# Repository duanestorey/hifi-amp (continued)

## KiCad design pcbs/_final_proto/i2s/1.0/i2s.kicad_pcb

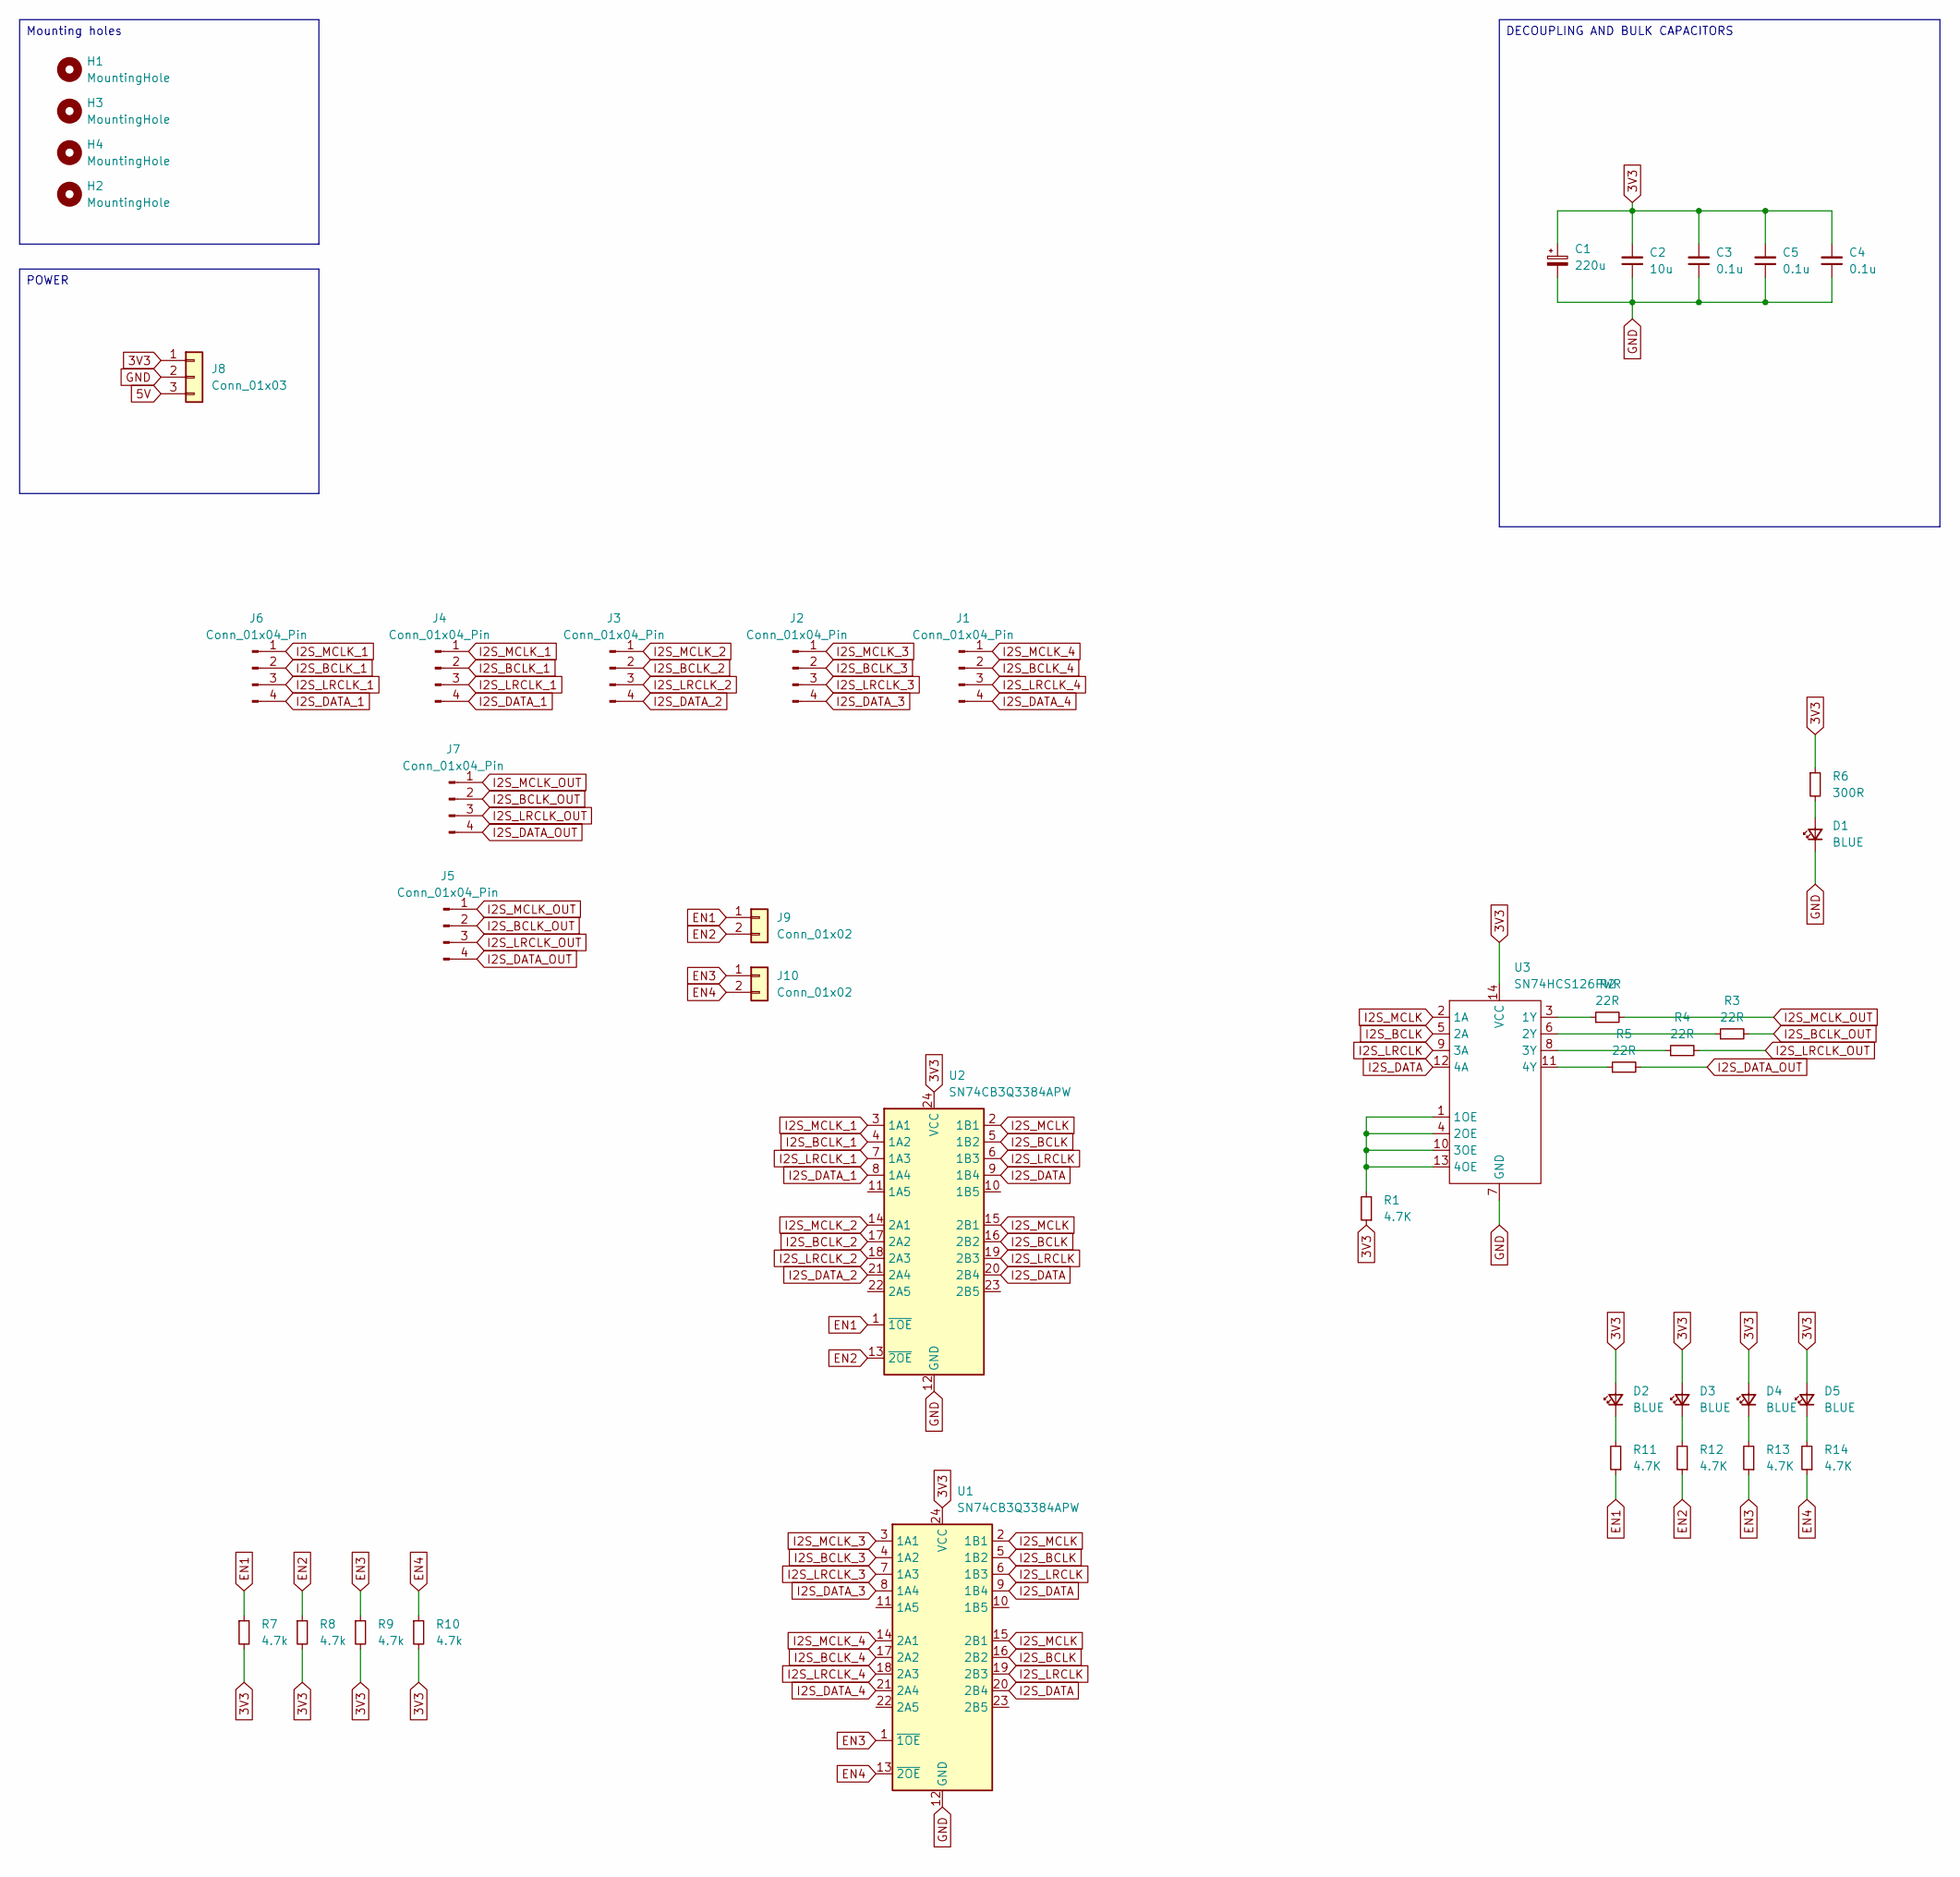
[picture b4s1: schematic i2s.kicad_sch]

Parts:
C1: 220u; CP_Elec_6.3x7.7
C2: 10u; C_1206_3216Metric_Pad1.33x1.80mm_HandSolder_Duane
C3, C4, C5: 0.1u; C_0805_2012Metric_Pad1.18x1.45mm_HandSolder_Duane
D1, D2, D3, D4, D5: BLUE; LED_0805_2012Metric_Pad_HandSolder_Duane
H1, H2, H3, H4: MountingHole; MountingHole_3.2mm_M3_DIN965_Pad_TopBottom
J1, J2, J3, J4, J6, J7: Conn_01x04_Pin; JST_PH_B4B-PH-K_1x04_P2.00mm_Vertical
J5: Conn_01x04_Pin; PinHeader_1x04_P2.54mm_Vertical
J8: Conn_01x03; JST_PH_B3B-PH-K_1x03_P2.00mm_Vertical
J9, J10: Conn_01x02; JST_PH_B2B-PH-K_1x02_P2.00mm_Vertical
R1, R11, R12, R13, R14: 4.7K; R_0805_2012Metric_Pad1.20x1.40mm_HandSolder_Duane
R2, R3, R4, R5: 22R; R_0805_2012Metric_Pad1.20x1.40mm_HandSolder_Duane
R6: 300R; R_0805_2012Metric_Pad1.20x1.40mm_HandSolder_Duane
R7, R8, R9, R10: 4.7k; R_0805_2012Metric_Pad1.20x1.40mm_HandSolder_Duane
U1, U2: SN74CB3Q3384APW; TSSOP-24_4.4x7.8mm_P0.65mm; Mouser SN74CB3Q3384APWR
U3: SN74HCS126PWR; TSSOP-14_4.4x5mm_P0.65mm; Mouser SN74HCS126PWR

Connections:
3V3: C1.1, C2.2, C3.2, C4.2, C5.2, D2.2 (A), D3.2 (A), D4.2 (A), D5.2 (A), J8.1, R1.1, R6.1, R7.2, R8.2, R9.2, R10.2, U1.24 (VCC), U2.24 (VCC), U3.14 (VCC)
5V: J8.3
EN1: J9.1, R7.1, R11.1, U2.1 (~1OE)
EN2: J9.2, R8.1, R12.1, U2.13 (~2OE)
EN3: J10.1, R9.1, R13.1, U1.1 (~1OE)
EN4: J10.2, R10.1, R14.1, U1.13 (~2OE)
GND: C1.2, C2.1, C3.1, C4.1, C5.1, D1.1 (K), J8.2, U1.12 (GND), U2.12 (GND), U3.7 (GND)
I2S_BCLK: U1.5 (1B2), U1.16 (2B2), U2.5 (1B2), U2.16 (2B2), U3.5 (2A)
I2S_BCLK_1: J4.2, J6.2, U2.4 (1A2)
I2S_BCLK_2: J3.2, U2.17 (2A2)
I2S_BCLK_3: J2.2, U1.4 (1A2)
I2S_BCLK_4: J1.2, U1.17 (2A2)
I2S_BCLK_OUT: J5.2, J7.2, R3.2
I2S_DATA: U1.9 (1B4), U1.20 (2B4), U2.9 (1B4), U2.20 (2B4), U3.12 (4A)
I2S_DATA_1: J4.4, J6.4, U2.8 (1A4)
I2S_DATA_2: J3.4, U2.21 (2A4)
I2S_DATA_3: J2.4, U1.8 (1A4)
I2S_DATA_4: J1.4, U1.21 (2A4)
I2S_DATA_OUT: J5.4, J7.4, R5.2
I2S_LRCLK: U1.6 (1B3), U1.19 (2B3), U2.6 (1B3), U2.19 (2B3), U3.9 (3A)
I2S_LRCLK_1: J4.3, J6.3, U2.7 (1A3)
I2S_LRCLK_2: J3.3, U2.18 (2A3)
I2S_LRCLK_3: J2.3, U1.7 (1A3)
I2S_LRCLK_4: J1.3, U1.18 (2A3)
I2S_LRCLK_OUT: J5.3, J7.3, R4.2
I2S_MCLK: U1.2 (1B1), U1.15 (2B1), U2.2 (1B1), U2.15 (2B1), U3.2 (1A)
I2S_MCLK_1: J4.1, J6.1, U2.3 (1A1)
I2S_MCLK_2: J3.1, U2.14 (2A1)
I2S_MCLK_3: J2.1, U1.3 (1A1)
I2S_MCLK_4: J1.1, U1.14 (2A1)
I2S_MCLK_OUT: J5.1, J7.1, R2.2
unnamed: D1.2 (A), R6.2
unnamed: D2.1 (K), R11.2
unnamed: D3.1 (K), R12.2
unnamed: D4.1 (K), R13.2
unnamed: D5.1 (K), R14.2
unnamed: R1.2, U3.1 (1OE), U3.4 (2OE), U3.10 (3OE), U3.13 (4OE)
unnamed: R2.1, U3.3 (1Y)
unnamed: R3.1, U3.6 (2Y)
unnamed: R4.1, U3.8 (3Y)
unnamed: R5.1, U3.11 (4Y)

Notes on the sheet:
DECOUPLING AND BULK CAPACITORS
Mounting holes
POWER

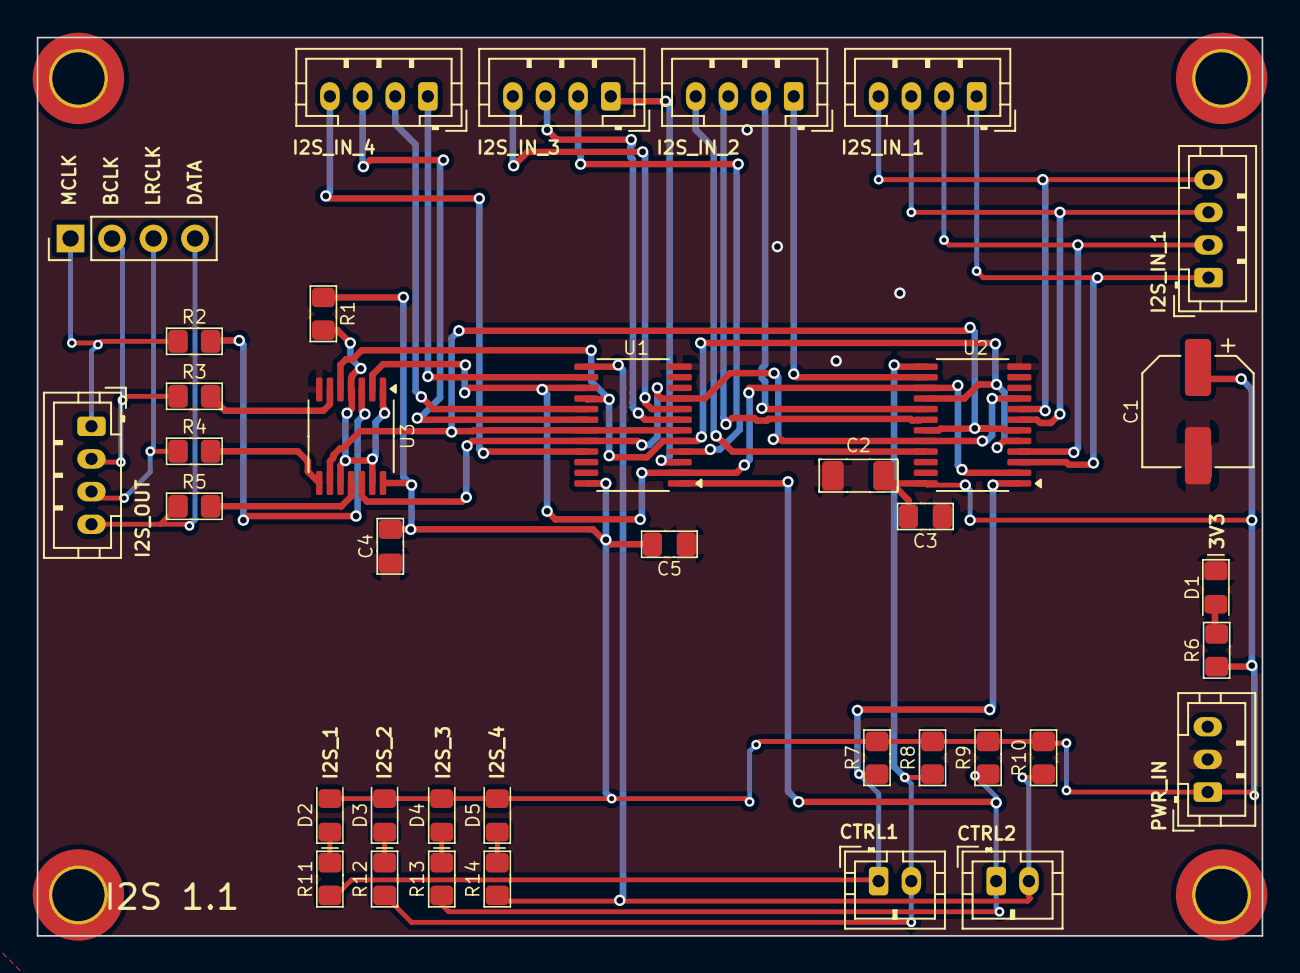
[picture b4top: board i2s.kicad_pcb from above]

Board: 2 copper layers, 75.0 x 55.0 mm, 41 parts (0 on the bottom side), 40 nets.

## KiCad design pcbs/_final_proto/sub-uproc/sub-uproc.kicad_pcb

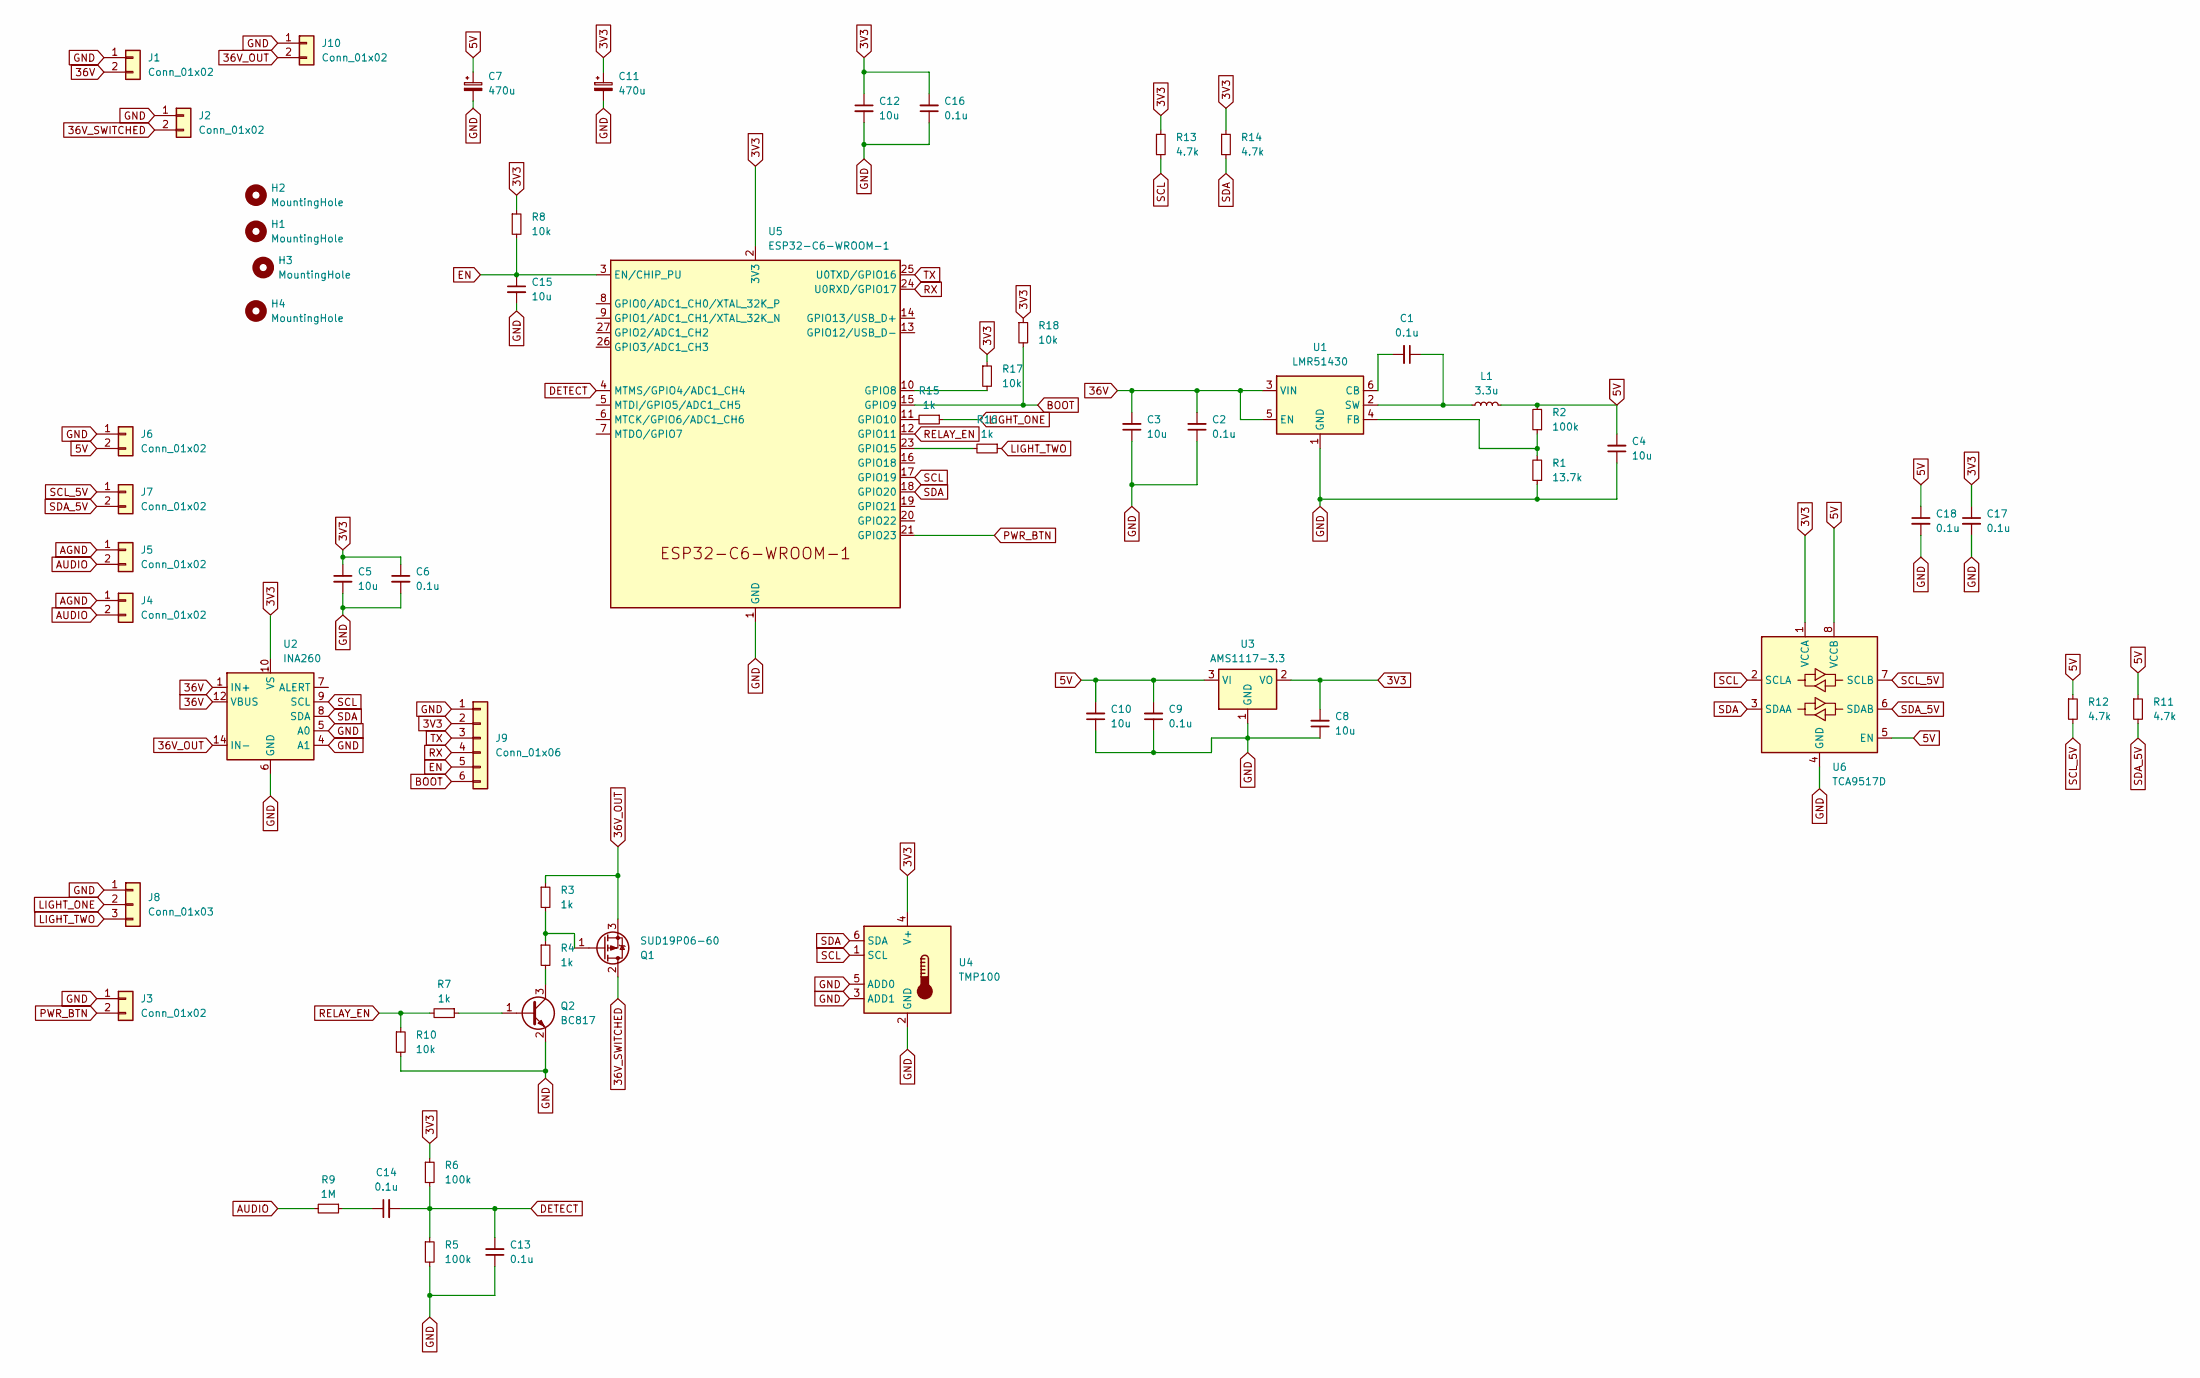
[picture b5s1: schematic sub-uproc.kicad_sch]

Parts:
C1, C2, C6, C9, C13, C14, C16, C17, C18: 0.1u; C_0805_2012Metric_Pad1.18x1.45mm_HandSolder_Duane
C3, C4, C5, C8, C10, C12, C15: 10u; C_1206_3216Metric_Pad1.33x1.80mm_HandSolder_Duane
C7, C11: 470u; CP_Elec_6.3x7.7
H1, H2, H3, H4: MountingHole; MountingHole_3.2mm_M3_DIN965_Pad_TopBottom
J1, J2, J4, J5, J6, J7, J10: Conn_01x02; TerminalBlock_Phoenix_PT-1,5-2-5.0-H_1x02_P5.00mm_Horizontal
J3: Conn_01x02; JST_PH_B2B-PH-K_1x02_P2.00mm_Vertical
J8: Conn_01x03; JST_PH_B3B-PH-K_1x03_P2.00mm_Vertical
J9: Conn_01x06; PinHeader_1x06_P2.54mm_Vertical
L1: 3.3u; L_Wuerth_HCI-7030
Q1: SUD19P06-60; TO-252-2
Q2: BC817; SOT-23
R1: 13.7k; R_0805_2012Metric_Pad1.20x1.40mm_HandSolder_Duane
R2, R5, R6: 100k; R_0805_2012Metric_Pad1.20x1.40mm_HandSolder_Duane
R3, R4, R7, R15, R16: 1k; R_0805_2012Metric_Pad1.20x1.40mm_HandSolder_Duane
R8, R10, R17, R18: 10k; R_0805_2012Metric_Pad1.20x1.40mm_HandSolder_Duane
R9: 1M; R_0805_2012Metric_Pad1.20x1.40mm_HandSolder_Duane
R11, R12, R13, R14: 4.7k; R_0805_2012Metric_Pad1.20x1.40mm_HandSolder_Duane
U1: LMR51430; SOT-23-6
U2: INA260; TSSOP-16_4.4x5mm_P0.65mm
U3: AMS1117-3.3; SOT-223-3_TabPin2
U4: TMP100; SOT-23-6
U5: ESP32-C6-WROOM-1
U6: TCA9517D; SOIC-8_3.9x4.9mm_P1.27mm

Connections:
3V3: C5.1, C6.1, C8.2, C11.1, C12.1, C16.2, C17.1, J9.2, R6.1, R8.1, R13.1, R14.1, R17.1, R18.1, U2.10 (VS), U3.2 (VO), U4.4 (V+), U5.2 (3V3), U6.1 (VCCA)
5V: C4.2, C7.1, C9.2, C10.2, C18.1, J6.2, L1.2, R2.2, R11.1, R12.1, U3.3 (VI), U6.5 (EN), U6.8 (VCCB)
36V: C2.2, C3.2, J1.2, U1.3 (VIN), U1.5 (EN), U2.1 (IN+), U2.2 (IN+), U2.3 (IN+), U2.12 (VBUS)
36V_OUT: J10.2, Q1.3 (S), R3.1, U2.14 (IN-), U2.15 (IN-), U2.16 (IN-)
36V_SWITCHED: J2.2, Q1.2 (D)
AGND: J4.1, J5.1
AUDIO: J4.2, J5.2, R9.2
BOOT: J9.6, R18.2, U5.15 (GPIO9)
DETECT: C13.2, C14.2, R5.1, R6.2, U5.4 (MTMS/GPIO4/ADC1_CH4)
EN: C15.1, J9.5, R8.2, U5.3 (EN/CHIP_PU)
GND: C2.1, C3.1, C4.1, C5.2, C6.2, C7.2, C8.1, C9.1, C10.1, C11.2, C12.2, C13.1, C15.2, C16.1, C17.2, C18.2, J1.1, J2.1, J3.1, J6.1, J8.1, J9.1, J10.1, Q2.2 (E), R1.1, R5.2, R10.2, U1.1 (GND), U2.4 (A1), U2.5 (A0), U2.6 (GND), U2.11 (GND), U3.1 (GND), U4.2 (GND), U4.3 (ADD1), U4.5 (ADD0), U5.1 (GND), U5.28 (GND), U5.29 (GND), U6.4 (GND)
LIGHT_ONE: J8.2, R15.1
LIGHT_TWO: J8.3, R16.1
unnamed: C14.1, R9.1
unnamed: Q1.1 (G), R3.2, R4.1
unnamed: Q2.1 (B), R7.1
unnamed: Q2.3 (C), R4.2
unnamed: C1.2, U1.6 (CB)
unnamed: R1.2, R2.1, U1.4 (FB)
unnamed: C1.1, L1.1, U1.2 (SW)
unnamed: R17.2, U5.10 (GPIO8)
unnamed: R15.2, U5.11 (GPIO10)
unnamed: R16.2, U5.23 (GPIO15)
PWR_BTN: J3.2, U5.21 (GPIO23)
RELAY_EN: R7.2, R10.1, U5.12 (GPIO11)
RX: J9.4, U5.24 (U0RXD/GPIO17)
SCL: R13.2, U2.9 (SCL), U4.1 (SCL), U5.17 (GPIO19), U6.2 (SCLA)
SCL_5V: J7.1, R12.2, U6.7 (SCLB)
SDA: R14.2, U2.8 (SDA), U4.6 (SDA), U5.18 (GPIO20), U6.3 (SDAA)
SDA_5V: J7.2, R11.2, U6.6 (SDAB)
TX: J9.3, U5.25 (U0TXD/GPIO16)

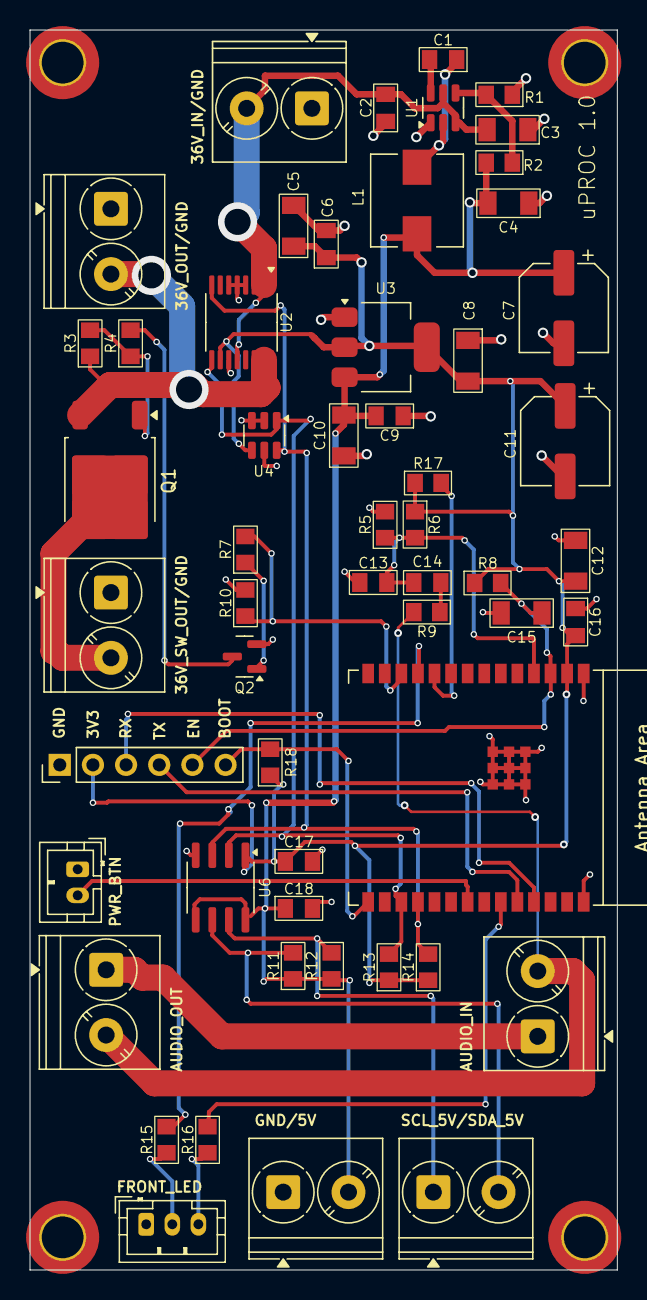
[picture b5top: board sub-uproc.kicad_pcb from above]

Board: 2 copper layers, 45.0 x 95.0 mm, 59 parts (0 on the bottom side), 31 nets.

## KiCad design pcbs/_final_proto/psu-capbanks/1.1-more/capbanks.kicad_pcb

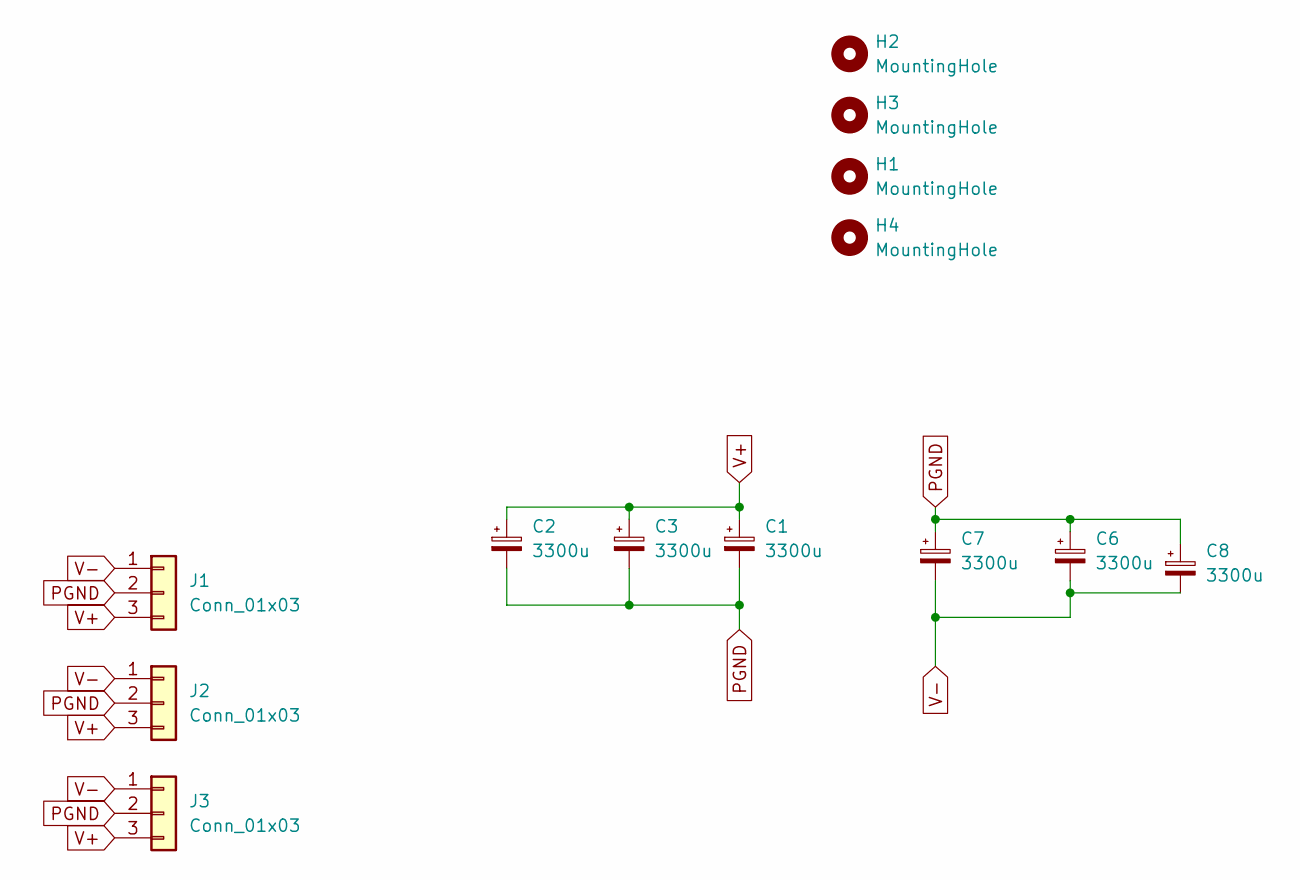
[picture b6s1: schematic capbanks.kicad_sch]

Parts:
C1, C2, C3, C6, C7, C8: 3300u; CP_Radial_D16.0mm_P7.50mm
H1, H2, H3, H4: MountingHole; MountingHole_3.2mm_M3_DIN965_Pad_TopBottom
J1, J2, J3: Conn_01x03; JST_VH_B3P-VH-B_1x03_P3.96mm_Vertical_Duane

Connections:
PGND: C1.2, C2.2, C3.2, C6.1, C7.1, C8.1, J1.2, J2.2, J3.2
V+: C1.1, C2.1, C3.1, J1.3, J2.3, J3.3
V-: C6.2, C7.2, C8.2, J1.1, J2.1, J3.1

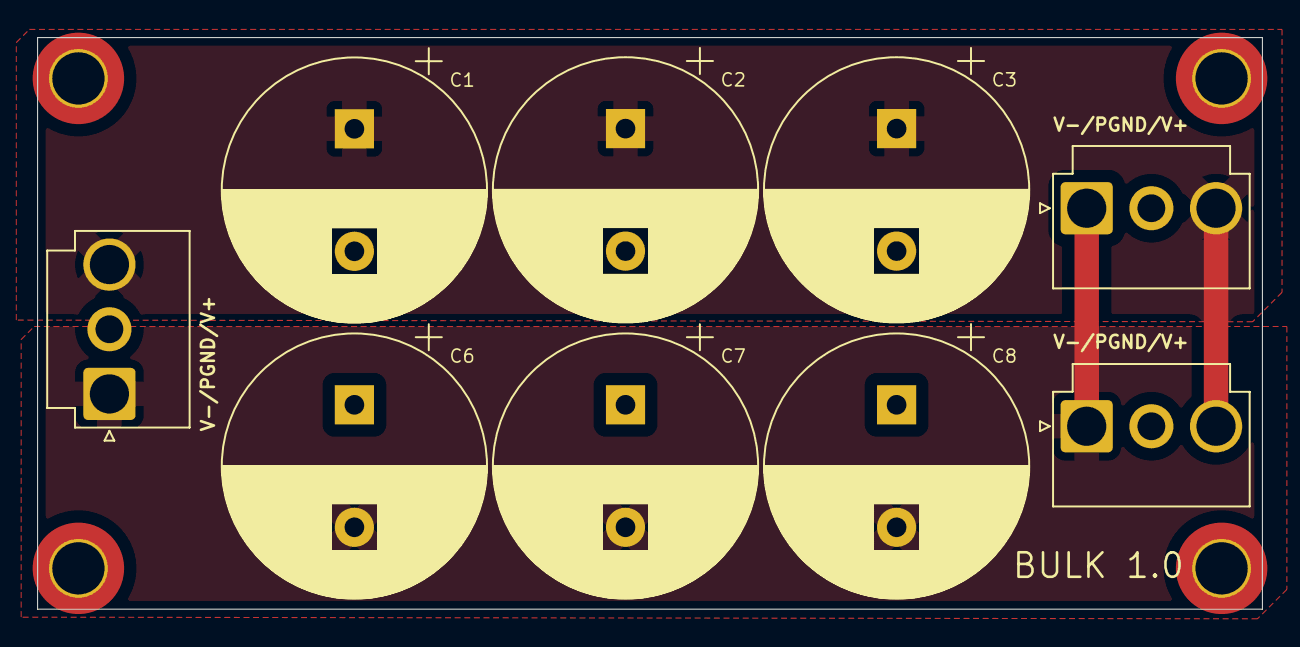
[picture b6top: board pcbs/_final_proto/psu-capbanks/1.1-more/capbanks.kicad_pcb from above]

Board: 2 copper layers, 75.0 x 35.0 mm, 13 parts (0 on the bottom side), 3 nets.

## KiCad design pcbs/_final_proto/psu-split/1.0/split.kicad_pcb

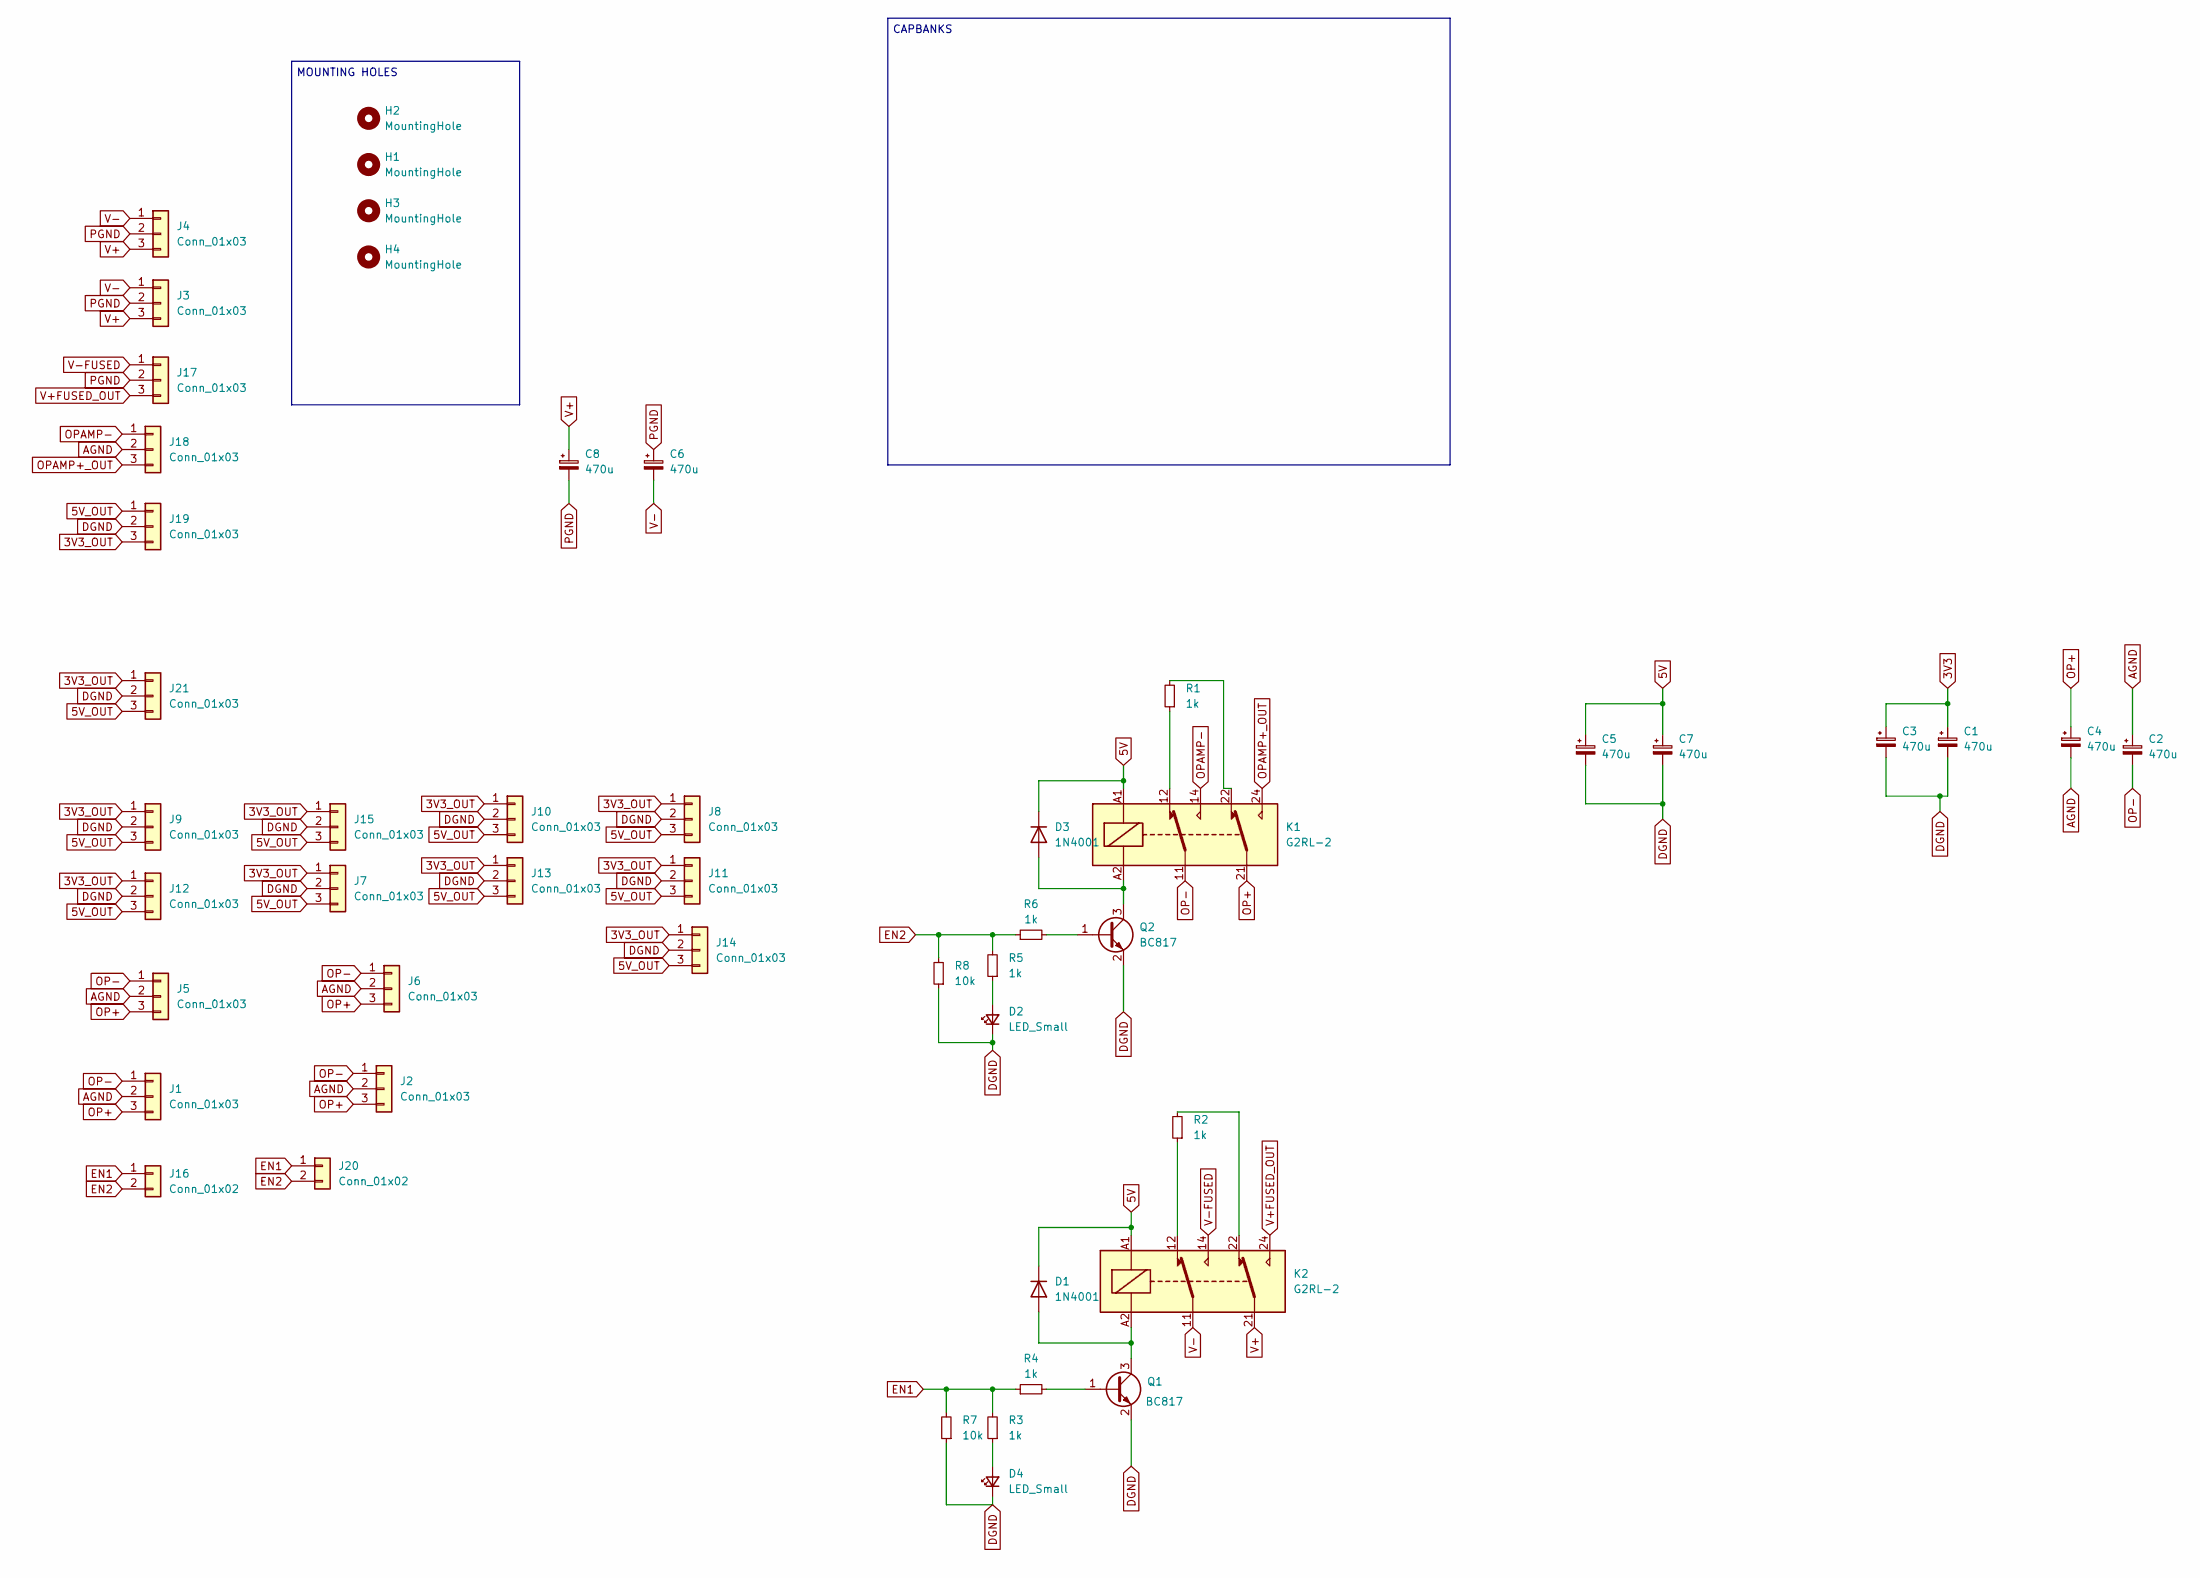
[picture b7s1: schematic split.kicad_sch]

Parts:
C1, C2, C3, C4, C5, C6, C7, C8: 470u; CP_Elec_6.3x7.7
D1, D3: 1N4001; D_SMA
D2, D4: LED_Small; LED_0805_2012Metric_Pad_HandSolder_Duane
H1, H2, H3, H4: MountingHole; MountingHole_3.2mm_M3_DIN965_Pad_TopBottom
J1, J2, J5, J6, J7, J8, J9, J10, J11, J12, J13, J14, J15, J21: Conn_01x03; JST_PH_B3B-PH-K_1x03_P2.00mm_Vertical
J3, J4, J17, J18, J19: Conn_01x03; TerminalBlock_Phoenix_PT-1,5-3-3.5-H_1x03_P3.50mm_Horizontal
J16: Conn_01x02; PinHeader_1x02_P2.54mm_Vertical
J20: Conn_01x02; JST_PH_B2B-PH-K_1x02_P2.00mm_Vertical
K1, K2: G2RL-2; Relay_DPDT_Omron_G2RL-2
Q1, Q2: BC817; SOT-23
R1, R2, R3, R4, R5, R6: 1k; R_0805_2012Metric_Pad1.20x1.40mm_HandSolder_Duane
R7, R8: 10k; R_0805_2012Metric_Pad1.20x1.40mm_HandSolder_Duane

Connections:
3V3: C1.1, C3.1
3V3_OUT: J7.1, J8.1, J9.1, J10.1, J11.1, J12.1, J13.1, J14.1, J15.1, J19.3, J21.1
5V: C5.1, C7.1, D1.1 (K), D3.1 (K), K1.A1, K2.A1
5V_OUT: J7.3, J8.3, J9.3, J10.3, J11.3, J12.3, J13.3, J14.3, J15.3, J19.1, J21.3
AGND: C2.1, C4.2, J1.2, J2.2, J5.2, J6.2, J18.2
DGND: C1.2, C3.2, C5.2, C7.2, D2.1 (K), D4.1 (K), J7.2, J8.2, J9.2, J10.2, J11.2, J12.2, J13.2, J14.2, J15.2, J19.2, J21.2, Q1.2 (E), Q2.2 (E), R7.1, R8.1
EN1: J16.1, J20.1, R3.2, R4.1, R7.2
EN2: J16.2, J20.2, R5.2, R6.1, R8.2
unnamed: D1.2 (A), K2.A2, Q1.3 (C)
unnamed: D2.2 (A), R5.1
unnamed: D3.2 (A), K1.A2, Q2.3 (C)
unnamed: D4.2 (A), R3.1
unnamed: K1.12, R1.1
unnamed: K1.22, R1.2
unnamed: K2.12, R2.1
unnamed: K2.22, R2.2
unnamed: Q1.1 (B), R4.2
unnamed: Q2.1 (B), R6.2
OP+: C4.1, J1.3, J2.3, J5.3, J6.3, K1.21
OP-: C2.2, J1.1, J2.1, J5.1, J6.1, K1.11
OPAMP+_OUT: J18.3, K1.24
OPAMP-: J18.1, K1.14
PGND: C6.1, C8.2, J3.2, J4.2, J17.2
V+: C8.1, J3.3, J4.3, K2.21
V+FUSED_OUT: J17.3, K2.24
V-: C6.2, J3.1, J4.1, K2.11
V-FUSED: J17.1, K2.14

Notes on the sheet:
MOUNTING HOLES
CAPBANKS

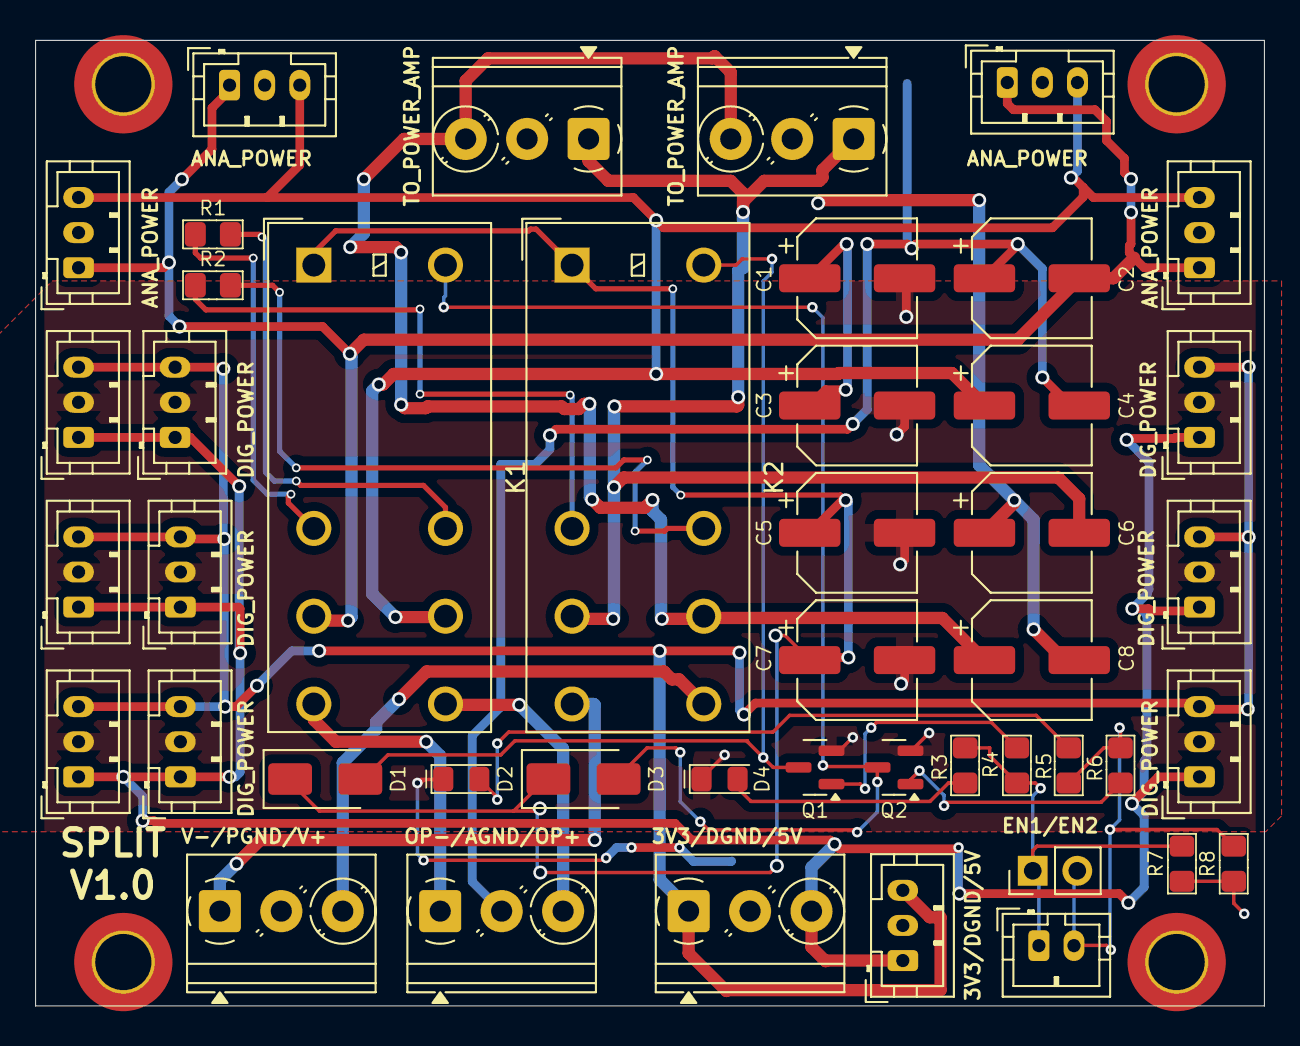
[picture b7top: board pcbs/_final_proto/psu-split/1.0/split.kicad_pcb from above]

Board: 2 copper layers, 70.0 x 55.0 mm, 49 parts (0 on the bottom side), 27 nets.
